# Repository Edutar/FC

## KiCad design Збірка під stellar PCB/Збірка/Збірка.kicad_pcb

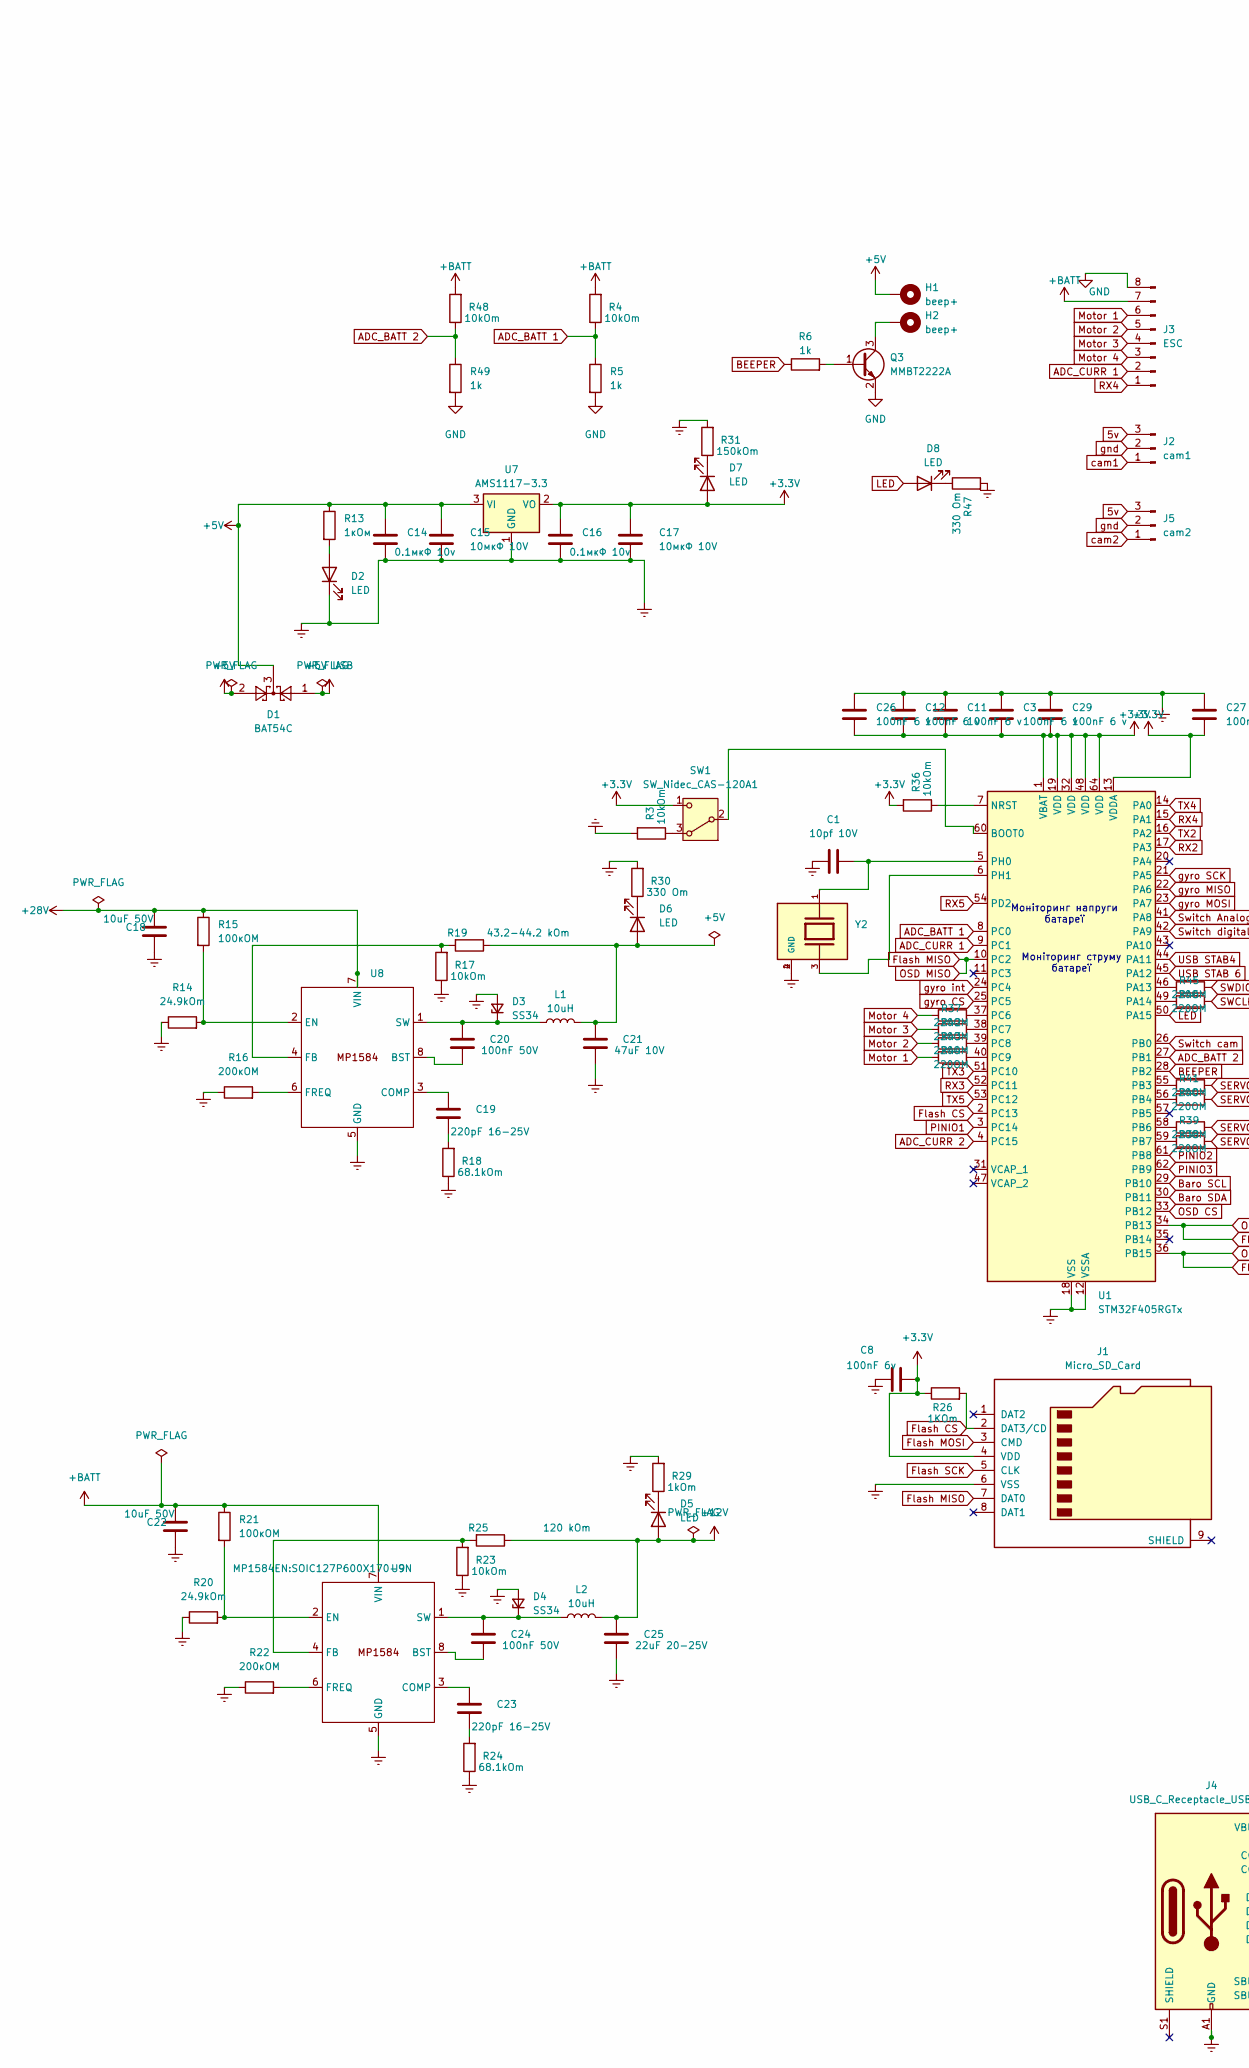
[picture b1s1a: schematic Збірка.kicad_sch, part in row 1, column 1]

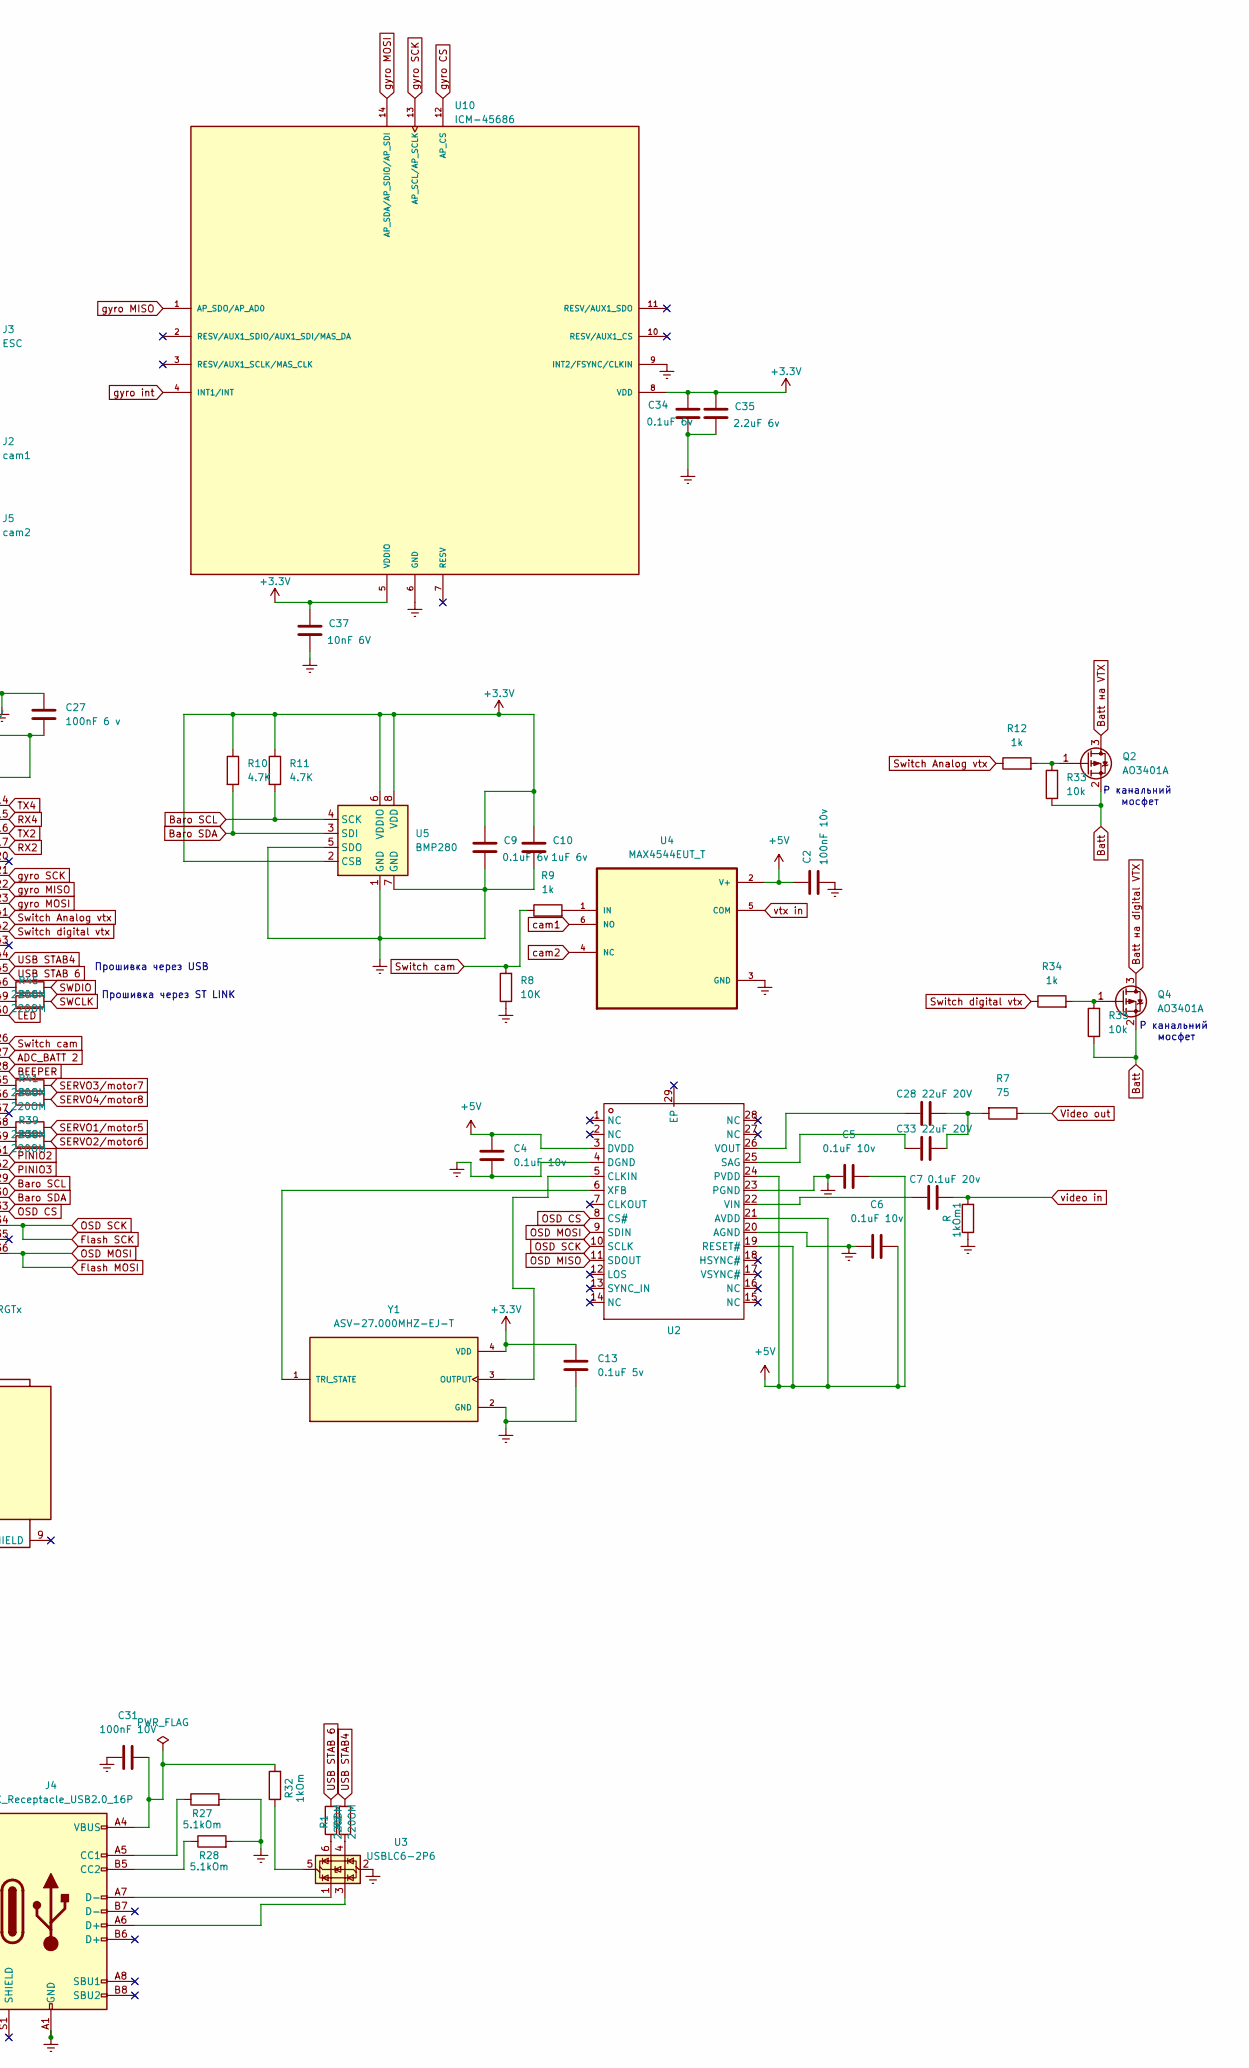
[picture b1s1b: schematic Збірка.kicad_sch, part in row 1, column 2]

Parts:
1kOm1: R; R_0402_1005Metric_Pad0.72x0.64mm_HandSolder
C1: 10pf 10V; C_0603_1608Metric_Pad1.08x0.95mm_HandSolder
C2: 100nF 10v; C_0603_1608Metric
C3, C11, C12, C26, C27, C29: 100nF 6 v; C_0603_1608Metric
C4, C5, C6: 0.1uF 10v; C_0805_2012Metric_Pad1.18x1.45mm_HandSolder
C7: 0.1uF 20v; C_0805_2012Metric
C8: 100nF 6v; C_0402_1005Metric
C9: 0.1uF 6v; C_0603_1608Metric
C10: 1uF 6v; C_0603_1608Metric
C13: 0.1uF 5v; C_0603_1608Metric
C14, C16: 0.1мкФ 10v; C_0603_1608Metric
C15, C17: 10мкФ 10V; C_0805_2012Metric
C18, C22: 10uF 50V; C_1210_3225Metric
C19, C23: 220pF 16-25V; C_1206_3216Metric
C20, C24: 100nF 50V; C_1210_3225Metric
C21: 47uF 10V; C_0805_2012Metric_Pad1.18x1.45mm_HandSolder
C25: 22uF 20-25V; C_1206_3216Metric
C28, C33: 22uF 20V; C_0805_2012Metric_Pad1.18x1.45mm_HandSolder
C31: 100nF 10V; C_0805_2012Metric
C34: 0.1uF 6v; C_0402_1005Metric
C35: 2.2uF 6v; C_0402_1005Metric
C37: 10nF 6V; C_0603_1608Metric
D1: BAT54C; SOT-23
D2, D5, D6, D7, D8: LED; LED_0402_1005Metric
D3, D4: SS34; D_SMA
H1, H2: beep+; SolderWirePad_1x01_SMD_1x2mm
J1: Micro_SD_Card; microSD_HC_Molex_47219-2001
J2: cam1; Samtec_T1M-03-X-S-RA_1x03-1MP_P1.0mm_Terminal_Horizontal
J3: ESC; Molex_200528-0080_1x08-1MP_P1.00mm_Horizontal
J4: USB_C_Receptacle_USB2.0_16P; USB_C_Receptacle_GCT_USB4105-xx-A_16P_TopMnt_Horizontal
J5: cam2; Samtec_T1M-03-X-S-RA_1x03-1MP_P1.0mm_Terminal_Horizontal
L1, L2: 10uH; IND_F1D1-060603W-100M
Q2, Q4: AO3401A; SOT-23
Q3: MMBT2222A; SOT-23
R1, R2, R37, R38, R39, R40, R41, R42, R43, R44, R45, R46: 220OM; R_0201_0603Metric
R3, R4, R17, R23, R36, R48: 10kOm; R_0402_1005Metric_Pad0.72x0.64mm_HandSolder
R5, R6, R9, R12, R34, R49: 1k; R_0201_0603Metric
R7: 75; R_0201_0603Metric
R8: 10K; R_0402_1005Metric_Pad0.72x0.64mm_HandSolder
R10, R11: 4.7K; R_0402_1005Metric
R13: 1кОм; R_0402_1005Metric_Pad0.72x0.64mm_HandSolder
R14, R20: 24.9kOm; R_0402_1005Metric_Pad0.72x0.64mm_HandSolder
R15: 100кОМ; R_0603_1608Metric_Pad0.98x0.95mm_HandSolder
R16, R22: 200кОМ; R_0603_1608Metric_Pad0.98x0.95mm_HandSolder
R18, R24: 68.1kOm; R_0402_1005Metric_Pad0.72x0.64mm_HandSolder
R19: 43.2-44.2 kOm; R_0603_1608Metric
R21: 100кОМ; R_0603_1608Metric
R25: 120 kOm; R_0603_1608Metric
R26: 1KOm; R_0402_1005Metric_Pad0.72x0.64mm_HandSolder
R27, R28: 5.1kOm; R_0402_1005Metric
R29, R32: 1kOm; R_0201_0603Metric
R30, R47: 330 Om; R_0201_0603Metric
R31: 150kOm; R_0201_0603Metric
R33, R35: 10k; R_0402_1005Metric_Pad0.72x0.64mm_HandSolder
SW1: SW_Nidec_CAS-120A1; Nidec_Copal_CAS-120A
U1: STM32F405RGTx; LQFP-64_10x10mm_P0.5mm
U2: SOP65P640X120-29N; Manufacturer Part AT7456E; LCSC Part Name AT7456E
U3: USBLC6-2P6; SOT-666
U4: MAX4544EUT_T; SOT95P280X145-6N
U5: BMP280; Bosch_LGA-8_2x2.5mm_P0.65mm_ClockwisePinNumbering
U7: AMS1117-3.3; SOT-223-3_TabPin2
U8, U9: SOIC127P600X170-9N
U10: ICM-45686; IC_ICM-45686; PARTREV 0.2
Y1: ASV-27.000MHZ-EJ-T; XTAL_ASV-27.000MHZ-EJ-T; PARTREV 09.02.14
Y2: C5S-8.000-16-3030-X-R; XTAL_C5S-8.000-16-3030-X-R; PARTREV N/A

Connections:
5v: J2.3, J5.3
+3.3V: C3.1, C8.2, C9.1, C10.1, C11.1, C12.1, C13.1, C16.1, C17.1, C26.1, C27.1, C29.1, C34.1, C35.1, C37.1, D7.2 (A), J1.4 (VDD), R10.1, R11.1, R26.1, R36.2, SW1.1 (C), U1.1 (VBAT), U1.13 (VDDA), U1.19 (VDD), U1.32 (VDD), U1.48 (VDD), U1.64 (VDD), U5.2 (CSB), U5.6 (VDDIO), U5.8 (VDD), U7.2 (VO), U10.5 (VDDIO), U10.8 (VDD), Y1.4 (VDD)
+5V: C2.1, C4.1, C5.2, C6.2, C14.1, C15.1, D1.2, D1.3, H1.1, R13.1, U2.3 (DVDD), U2.19 (RESET#), U2.21 (AVDD), U2.24 (PVDD), U4.2 (V+), U7.3 (VI)
+5V USB: D1.1
+12V: C25.1, D5.2 (A), L2.2, R25.1
+28V: C18.1, R15.1, U8.7 (VIN)
+BATT: C22.1, J3.7, R4.2, R21.1, R48.2, U9.7 (VIN)
<NO NET>: 1kOm1.1, C1.2, C2.2, C3.2, C4.2, C5.1, C6.1, C8.1, C9.2, C10.2, C11.2, C12.2, C13.2, C14.2, C15.2, C16.2, C17.2, C26.2, C27.2, C29.2, C31.2, D2.1 (K), J1.6 (VSS), J4.A1 (GND), J4.A12 (GND), J4.B1 (GND), J4.B12 (GND), R3.2, R8.1, U1.12 (VSSA), U1.18 (VSS), U1.63 (VSS), U2.4 (DGND), U2.20 (AGND), U2.23 (PGND), U4.3 (GND), U5.1 (GND), U5.5 (SDO), U5.7 (GND), U7.1 (GND), Y1.2 (GND)
ADC_BATT 1: R4.1, R5.1, U1.8 (PC0)
ADC_BATT 2: R48.1, R49.1, U1.27 (PB1)
ADC_CURR 1: J3.2, U1.9 (PC1)
ADC_CURR 2: U1.4 (PC15)
BEEPER: R6.1, U1.28 (PB2)
Baro SCL: R11.2, U1.29 (PB10), U5.4 (SCK)
Baro SDA: R10.2, U1.30 (PB11), U5.3 (SDI)
Batt: Q2.2 (S), Q4.2 (S), R33.1, R35.1
Batt на VTX: Q2.3 (D)
Batt на digital VTX: Q4.3 (D)
Earth: C18.2, C21.2, C22.2, C25.2, C34.2, C35.2, C37.2, D3.2 (A), D4.2 (A), R14.1, R16.1, R17.1, R18.1, R20.1, R22.1, R23.1, R24.1, R27.2, R28.2, R29.2, R30.2, R31.2, R47.2, U3.2 (GND), U8.5 (GND), U9.5 (GND), U10.6 (GND), U10.9 (INT2/FSYNC/CLKIN), Y2.2 (GND), Y2.4 (GND)
Flash CS: J1.2 (DAT3/CD), R26.2, U1.2 (PC13)
Flash MISO: J1.7 (DAT0), U1.10 (PC2), U2.11 (SDOUT)
Flash MOSI: J1.3 (CMD), U1.36 (PB15), U2.9 (SDIN)
Flash SCK: J1.5 (CLK), U1.34 (PB13), U2.10 (SCLK)
GND: J3.8, Q3.2 (E), R5.2, R49.2
LED: D8.2 (A), U1.50 (PA15)
Motor 1: J3.6, R44.1
Motor 2: J3.5, R43.1
Motor 3: J3.4, R42.1
Motor 4: J3.3, R37.1
unnamed: C19.2, R18.2
unnamed: C23.2, R24.2
unnamed: C28.1, C33.1, R7.2
unnamed: C31.1, J4.A4 (VBUS), J4.A9 (VBUS), J4.B4 (VBUS), J4.B9 (VBUS), R32.2
unnamed: D2.2 (A), R13.2
unnamed: C20.1, D3.1 (K), L1.1, U8.1 (SW)
unnamed: C24.1, D4.1 (K), L2.1, U9.1 (SW)
unnamed: D5.1 (K), R29.1
unnamed: C21.1, D6.2 (A), L1.2, R19.1
unnamed: D6.1 (K), R30.1
unnamed: D7.1 (K), R31.1
unnamed: D8.1 (K), R47.1
unnamed: J4.A5 (CC1), R27.1
unnamed: J4.B5 (CC2), R28.1
unnamed: J4.A6 (D+), U3.3 (I/O2)
unnamed: J4.A7 (D-), U3.1 (I/O1)
unnamed: Q2.1 (G), R12.2, R33.2
unnamed: Q3.1 (B), R6.2
unnamed: H2.1, Q3.3 (C)
unnamed: Q4.1 (G), R34.2, R35.2
unnamed: R1.1, U3.6 (I/O1)
unnamed: R2.1, U3.4 (I/O2)
unnamed: R3.1, SW1.3 (A)
unnamed: SW1.2 (B), U1.60 (BOOT0)
unnamed: R36.1, U1.7 (NRST)
unnamed: R45.1, U1.46 (PA13)
unnamed: R46.1, U1.49 (PA14)
unnamed: R41.1, U1.55 (PB3)
unnamed: R40.1, U1.56 (PB4)
unnamed: R39.1, U1.58 (PB6)
unnamed: R38.1, U1.59 (PB7)
unnamed: R37.2, U1.37 (PC6)
unnamed: R42.2, U1.38 (PC7)
unnamed: R43.2, U1.39 (PC8)
unnamed: R44.2, U1.40 (PC9)
unnamed: C1.1, U1.5 (PH0), Y2.1
unnamed: U1.6 (PH1), Y2.3
unnamed: U2.5 (CLKIN), Y1.3 (OUTPUT)
unnamed: C33.2, U2.25 (SAG)
unnamed: C7.2, U2.22 (VIN)
unnamed: C28.2, U2.26 (VOUT)
unnamed: U2.6 (XFB), Y1.1 (TRI_STATE)
unnamed: R32.1, U3.5 (VBUS)
unnamed: R9.2, U4.1 (IN)
unnamed: C20.2, U8.8 (BST)
unnamed: C19.1, U8.3 (COMP)
unnamed: R14.2, R15.2, U8.2 (EN)
unnamed: R17.2, R19.2, U8.4 (FB)
unnamed: R16.2, U8.6 (FREQ)
unnamed: C24.2, U9.8 (BST)
unnamed: C23.1, U9.3 (COMP)
unnamed: R20.2, R21.2, U9.2 (EN)
unnamed: R23.2, R25.2, U9.4 (FB)
unnamed: R22.2, U9.6 (FREQ)
OSD CS: U1.33 (PB12), U2.8 (CS#)
PINIO1: U1.3 (PC14)
PINIO2: U1.61 (PB8)
PINIO3: U1.62 (PB9)
RX2: U1.17 (PA3)
RX3: U1.52 (PC11)
RX4: J3.1, U1.15 (PA1)
RX5: U1.54 (PD2)
SERVO1/motor5: R39.2
SERVO2/motor6: R38.2
SERVO3/motor7: R41.2
SERVO4/motor8: R40.2
SWCLK: R46.2
SWDIO: R45.2
Switch Analog vtx: R12.1, U1.41 (PA8)
Switch cam: R8.2, R9.1, U1.26 (PB0)
Switch digital vtx: R34.1, U1.42 (PA9)
TX2: U1.16 (PA2)
TX3: U1.51 (PC10)
TX4: U1.14 (PA0)
TX5: U1.53 (PC12)
USB STAB4: R2.2, U1.44 (PA11)
USB STAB 6: R1.2, U1.45 (PA12)
Video out: R7.1
cam1: J2.1, U4.6 (NO)
cam2: J5.1, U4.4 (NC)
gnd: J2.2, J5.2
gyro CS: U1.25 (PC5), U10.12 (AP_CS)
gyro MISO: U1.22 (PA6), U10.1 (AP_SDO/AP_AD0)
gyro MOSI: U1.23 (PA7), U10.14 (AP_SDA/AP_SDIO/AP_SDI)
gyro SCK: U1.21 (PA5), U10.13 (AP_SCL/AP_SCLK)
gyro int: U1.24 (PC4), U10.4 (INT1/INT)
video in: 1kOm1.2, C7.1
vtx in: U4.5 (COM)

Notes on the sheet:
Прошивка через ST LINK
Прошивка через USB
P канальний мосфет
Моніторинг напруги батареї
Моніторинг струму батареї

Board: 6 copper layers, 116 parts (0 on the bottom side), 95 nets, no tracks yet.
